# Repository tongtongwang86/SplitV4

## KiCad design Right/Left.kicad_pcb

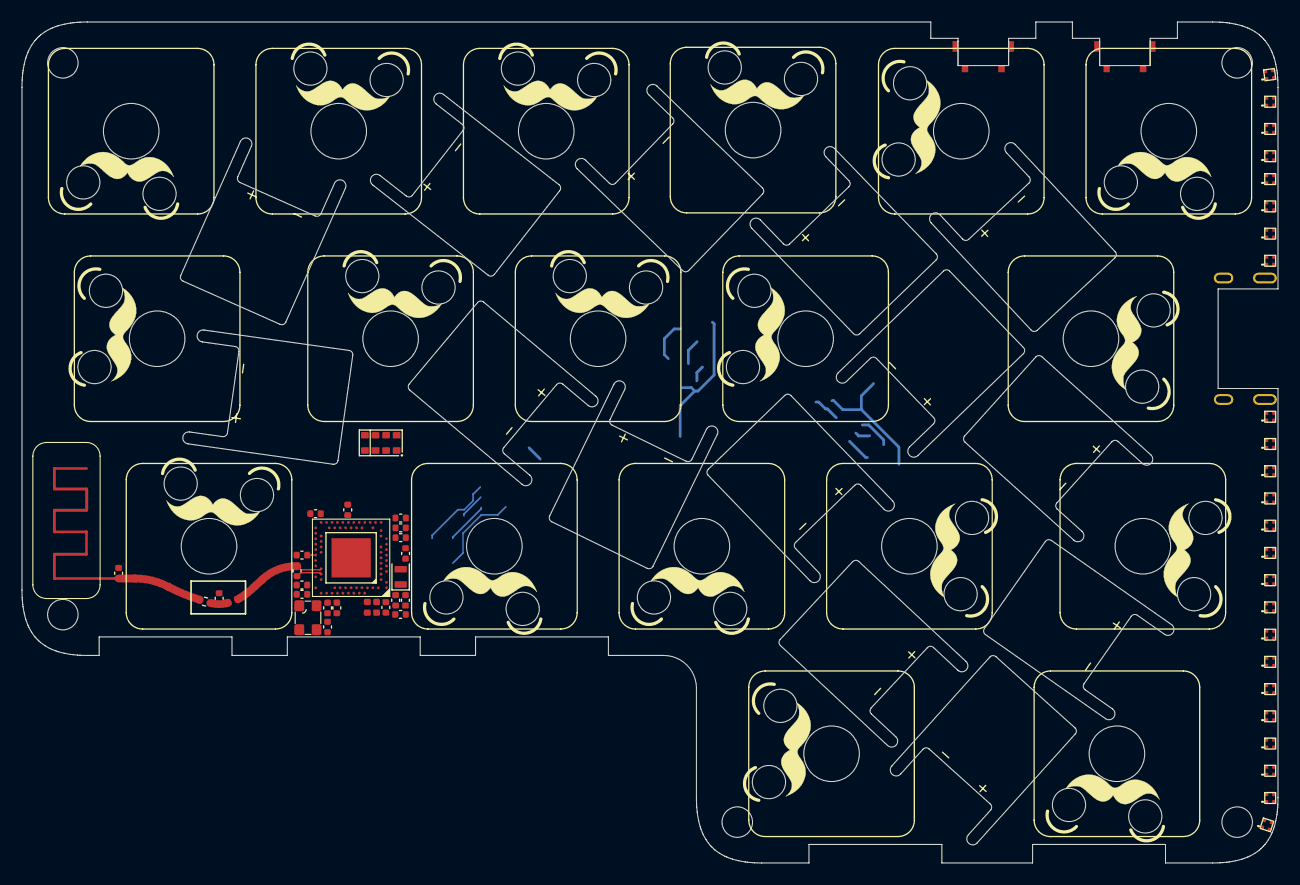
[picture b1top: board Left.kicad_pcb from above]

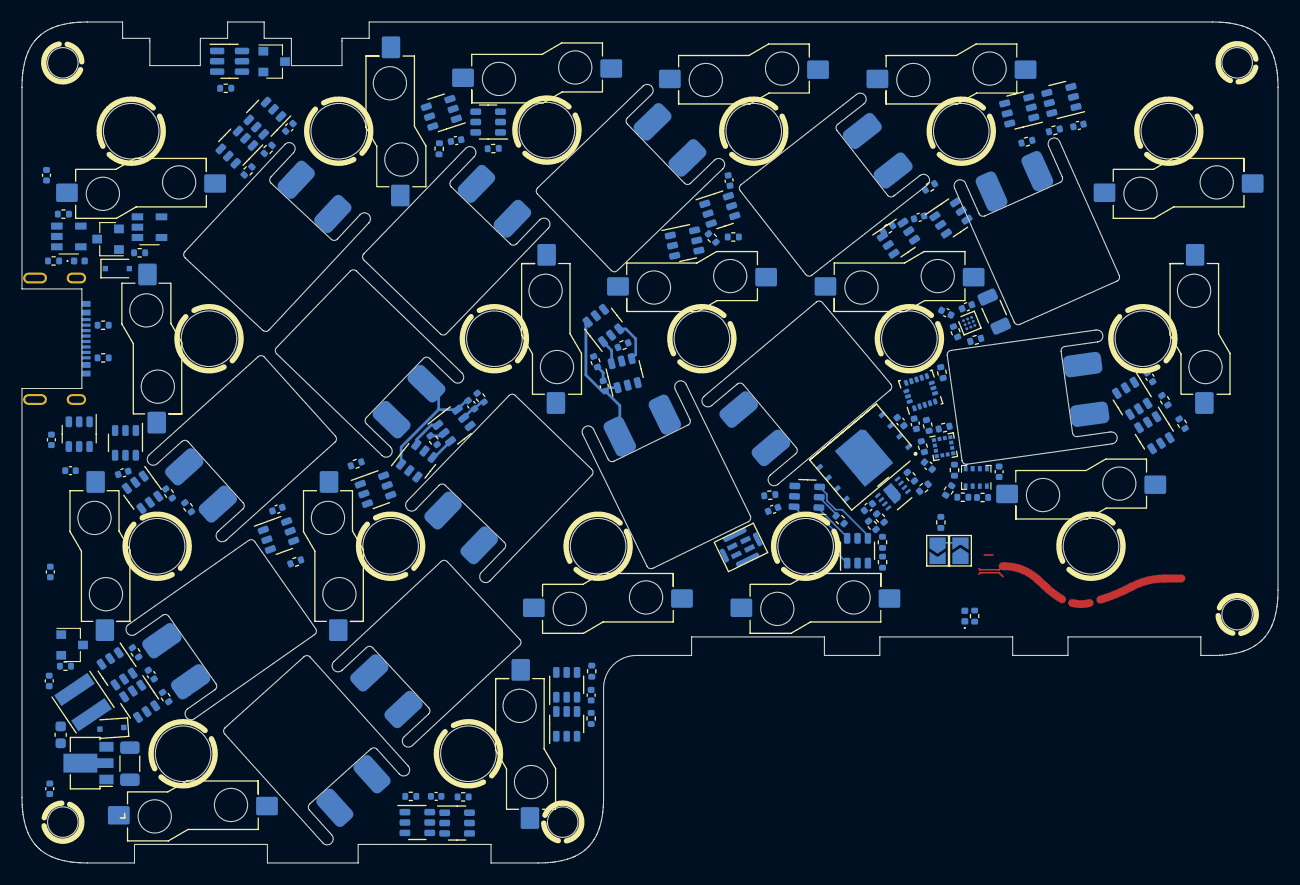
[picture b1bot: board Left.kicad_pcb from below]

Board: 4 copper layers, 115.3 x 77.2 mm, 202 parts (134 on the bottom side), 156 nets.

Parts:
AE1: Antenna; 2.4GHz-meander-antenna-v2
B1, B2, B3, B4, B5, B6, B7, B8, B9, B10, B11, B12, B13, B14: Battery; BatteryV2
C1, C2, C3, C4, C5, C6, C7, C8, C9, C10, C11, C12, C13, C14, C16, C17, C18, C19, C20, C21, C26, C31, C32, C33, C45, C46: 100nF; C_0402_1005Metric
C22, C23, C36, C37: 12pF; C_0402_1005Metric
C24, C25, C27: 4.7uF; C_0402_1005Metric
C28, C29, C47: 1uF; C_0402_1005Metric
C30: 47nF; C_0402_1005Metric
C34: 820pF; C_0402_1005Metric
C35, C39: 1pF; C_0402_1005Metric
C38: 100pF; C_0402_1005Metric
C40: 1.5pF; C_0402_1005Metric
C41: 0.47uF; C_0402_1005Metric
C42, C48, C49: 0.1uF; C_0402_1005Metric
C43: 47uF; C_0603_1608Metric
C44: 100uF; C_1206_3216Metric
D1, D3: 1N5819; D_SOD-323F
D2: BLUE; LED_0402_1005Metric
D4: RED; LED_0402_1005Metric
J1: USB-C USB 2.0 MC-372; USB-C_C168688
JP1, JP2: SolderJumper_2_Open; SolderJumper-2_P1.3mm_Open_TrianglePad1.0x1.5mm
L1: 15nH; L_0402_1005Metric
L2: 10uH; L_0402_1005Metric
L3: 3.9nH; L_0402_1005Metric
L4: 22uH; L_Taiyo-Yuden_NR-40xx
Q1, Q2: AO3407; SOT-23
Q3, Q4, Q5, Q6, Q7, Q8, Q9, Q10, Q19, Q20, Q21, Q22, Q27, Q28: 8205A; SOT-23-6-Small
Q11, Q12, Q13, Q14, Q15, Q16, Q17, Q18, Q23, Q24, Q25, Q26, Q30, Q31: DW01; SOT-23-6-Small
Q33: AO3400A; SOT-23
R1: 100K; R_0402_1005Metric
R2, R33, R34, R35: 5.1K; R_0402_1005Metric
R3, R4, R5, R6, R7, R8, R9, R10, R19, R20, R21, R22, R27, R28, R38, R44: 1K; R_0402_1005Metric
R11, R12, R13, R14, R15, R16, R17, R18, R23, R24, R25, R26, R30, R31: 100; R_0402_1005Metric
R36, R37, R47: 4.7K; R_0402_1005Metric
R39: 0R; R_0402_1005Metric
R40: 820K; R_0402_1005Metric
R41, R46: 2M; R_0402_1005Metric
R42: 0.010; R_1206_3216Metric
R43: 10k; R_0402_1005Metric
R45: 12K; R_0402_1005Metric
R48, R49, R50, R51, R52, R53, R54, R55, R56: 10K; R_0402_1005Metric
TH1: Thermistor_NTC; R_0402_1005Metric
U1: AP2112K-3.3; SOT-23-5
U2, U29: Button
U3: MAX16054; SOT-23-6
U4, U5, U6, U7, U8, U9, U10, U11, U12, U13, U14, U15, U16, U17, U18, U19, U20, U21, U22, U23, U24, U25, U26, U27: WS2812B_-_1010; Led-ARGB
U28: USBLC6-2SC6; SOT-23-6-Small
U30: nRF52840_aQFN73; AQFN-73-1EP_7x7mm_P0.5mm_NRF52840-custom
U31: MAX17055; WLP-9_1.448x1.468mm_Layout3x3_P0.4mm_Ball0.27mm_Pad0.25mm
U32: BL8530_501SM; SOT-89-3
U33: TP4054; SOT-23-5
U34: LSM6DS33; LGA-16_3x3mm_P0.5mm_LayoutBorder3x5y
U35: BMP280; Bosch_LGA-8_2x2.5mm_P0.65mm_ClockwisePinNumbering
U36: SHT30-DIS; Sensirion_DFN-8-1EP_2.5x2.5mm_P0.5mm_EP1.1x1.7mm
U37: APDS-9960
U38: PDM_Mic; SPK0415HM4H
U39: GD25Q; WSON8
U40: LIS3MDL; LGA-12_2x2mm_P0.5mm
X1: 32.768 kHz; Crystal_SMD_2012-2Pin_2.0x1.2mm
X2: 32MHZ; crystal 32mhz

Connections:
/BAROMETRIC/CSB: R48.1, U35.2 (CSB)
/BAROMETRIC/NRF_VDD: C24.2, C25.2, C28.2, C31.2, C32.2, C33.2, C43.1, C45.2, C46.1, C47.2, C48.2, L4.1, R35.2, R36.2, R37.2, R48.2, R49.2, R51.2, R52.2, R53.2, R54.2, R55.2, R56.2, U1.5 (VOUT), U30.A22 (VDD), U30.AD14 (VDD), U30.AD23 (VDD), U30.B1 (VDD), U30.W1 (VDD), U30.Y2 (VDDH), U34.1 (VDDIO), U34.5 (CS), U34.16 (VDD), U35.6 (VDDIO), U35.8 (VDD), U36.5 (VDD), U36.6 (~RESET), U37.5 (LEDA), U37.8 (VDD), U38.1 (VDD), U39.8 (VCC), U40.5 (VDD), U40.6 (VDDIO), U40.10 (CS)
/BAROMETRIC/SDO: R50.2, U35.5 (SDO)
/ExtVcc/GND_EN: Q33.1 (G), R46.1, U30.R1 (TRACEDATA3/P1.09)
/FLASH/QSPI_CS: U30.AD16 (P0.20), U39.1 (SSEL)
/FLASH/QSPI_DATA0: U30.AD12 (P0.17), U39.5 (MOSI)
/FLASH/QSPI_DATA1: U30.AD18 (P0.22), U39.2 (MISO)
/FLASH/QSPI_DATA2: U30.AC19 (P0.23), U39.3 (WP#/IO2)
/FLASH/QSPI_DATA3: U30.AC17 (P0.21), U39.7 (HOLD#/IO3)
/FLASH/QSPI_SCK: U30.AC15 (P0.19), U39.6 (SCK)
/Filter&Reg/VBAT: C42.1, Q1.3 (D), Q2.3 (D), R40.1, U31.B1 (BATT), U33.3 (VBAT)
/FuelGauge/BatteryPin: R40.2, R41.1, U30.J1 (AIN2/P0.04)
/Gyro/Gyro_Interupt: R47.1, U30.B19 (P1.11), U34.7 (INT1)
/LEDLane/DIN: U27.4 (DI), U30.W24 (P1.02)
/LEDLane/Led_Ground: Q33.3 (D), U4.3 (GND), U5.3 (GND), U6.3 (GND), U7.3 (GND), U8.3 (GND), U9.3 (GND), U10.3 (GND), U11.3 (GND), U12.3 (GND), U13.3 (GND), U14.3 (GND), U15.3 (GND), U16.3 (GND), U17.3 (GND), U18.3 (GND), U19.3 (GND), U20.3 (GND), U21.3 (GND), U22.3 (GND), U23.3 (GND), U24.3 (GND), U25.3 (GND), U26.3 (GND), U27.3 (GND)
/LEDLane/Led_Vin: C16.2, C17.2, C18.2, C19.2, C20.2, C44.1, D3.1 (K), U4.2 (VDD), U5.2 (VDD), U6.2 (VDD), U7.2 (VDD), U8.2 (VDD), U9.2 (VDD), U10.2 (VDD), U11.2 (VDD), U12.2 (VDD), U13.2 (VDD), U14.2 (VDD), U15.2 (VDD), U16.2 (VDD), U17.2 (VDD), U18.2 (VDD), U19.2 (VDD), U20.2 (VDD), U21.2 (VDD), U22.2 (VDD), U23.2 (VDD), U24.2 (VDD), U25.2 (VDD), U26.2 (VDD), U27.2 (VDD), U32.2 (OUT)
/LIGHT/APDS_IRQ: R54.1, U30.AD22 (TRACEDATA0/P1.00), U37.2 (INT)
/MCU/BatOffPin: R2.1, U3.3 (CLEAR), U30.Y23 (P1.01)
/MCU/D+: U28.4 (2), U30.AD6 (D+)
/MCU/D-: U28.6 (1), U30.AD4 (D-)
/MCU/PDM_CLK: U30.H2 (P0.27), U38.3 (CLK)
/MCU/PDM_DAT: U30.G1 (P0.26), U38.4 (DATA)
B1-: B1.1 (-), C1.2, Q3.1 (S1), Q11.6 (GND)
B2-: B2.1 (-), C2.2, Q4.1 (S1), Q12.6 (GND)
B3-: B3.1 (-), C3.2, Q5.1 (S1), Q13.6 (GND)
B4-: B4.1 (-), C4.2, Q6.1 (S1), Q14.6 (GND)
B5-: B5.1 (-), C5.2, Q7.1 (S1), Q15.6 (GND)
B6-: B6.1 (-), C6.2, Q8.1 (S1), Q16.6 (GND)
B7-: B7.1 (-), C7.2, Q9.1 (S1), Q17.6 (GND)
B8-: B8.1 (-), C8.2, Q10.1 (S1), Q18.6 (GND)
B9-: B9.1 (-), C9.2, Q19.1 (S1), Q23.6 (GND)
B10-: B10.1 (-), C10.2, Q20.1 (S1), Q24.6 (GND)
B11-: B11.1 (-), C11.2, Q21.1 (S1), Q25.6 (GND)
B12-: B12.1 (-), C12.2, Q22.1 (S1), Q26.6 (GND)
B13-: B13.1 (-), C13.2, Q27.1 (S1), Q30.6 (GND)
B14-: B14.1 (-), C14.2, Q28.1 (S1), Q31.6 (GND)
B+: B1.2 (+), B2.2 (+), B3.2 (+), B4.2 (+), B5.2 (+), B6.2 (+), B7.2 (+), B8.2 (+), B9.2 (+), B10.2 (+), B11.2 (+), B12.2 (+), B13.2 (+), B14.2 (+), Q2.2 (S), R11.1, R12.1, R13.1, R14.1, R15.1, R16.1, R17.1, R18.1, R23.1, R24.1, R25.1, R26.1, R30.1, R31.1, U3.6 (VCC)
CC1: J1.A5 (CC1), R33.1
CC2: J1.B5 (CC2), R34.1
GND: C16.1, C17.1, C18.1, C19.1, C20.1, C21.2, C22.2, C23.2, C24.1, C25.1, C26.1, C27.1, C28.1, C29.2, C30.2, C31.1, C32.1, C33.1, C34.1, C35.1, C36.1, C37.1, C38.2, C39.1, C40.2, C41.1, C42.2, C43.2, C44.2, C45.1, C46.2, C47.1, C48.1, C49.2, J1.A1 (GND), Q33.2 (S), R1.2, R33.2, R34.2, R38.2, R41.2, R42.2, R45.2, R46.2, R47.2, R50.1, U1.2 (GND), U28.2 (G), U29.2, U30.B7 (VSS), U30.EP (VSS), U30.F23 (VSS_PA), U31.A3 (CSN), U32.1 (GND), U33.2 (VSS), U34.4 (SDO), U34.8 (GND), U34.9 (GND), U34.10 (GND), U34.11 (GND), U34.12 (GND), U34.13 (GND), U34.15 (GND), U35.1 (GND), U35.7 (GND), U36.2 (ADDR), U36.7 (R), U36.8 (VSS), U36.9 (VSS), U37.6 (GND), U38.2 (L/R), U38.5 (GND), U38.6 (GND), U38.7 (GND), U38.8 (GND), U39.4 (VSS), U40.2 (GND), U40.3 (GND), U40.9 (SDO), U40.12 (GND), X2.2, X2.4
GND1: Q3.3 (S2), Q4.3 (S2), Q5.3 (S2), Q6.3 (S2), Q7.3 (S2), Q8.3 (S2), Q9.3 (S2), Q10.3 (S2), Q19.3 (S2), Q20.3 (S2), Q21.3 (S2), Q22.3 (S2), Q27.3 (S2), Q28.3 (S2), R2.2, R3.1, R4.1, R5.1, R6.1, R7.1, R8.1, R9.1, R10.1, R19.1, R20.1, R21.1, R22.1, R27.1, R28.1, R42.1, TH1.2, U2.2, U3.2 (GND), U31.C3 (CSP)
unnamed: AE1.1 (A), C40.1, R39.2
unnamed: C1.1, Q11.5 (VCC), R11.2
unnamed: C2.1, Q12.5 (VCC), R12.2
unnamed: C3.1, Q13.5 (VCC), R13.2
unnamed: C4.1, Q14.5 (VCC), R14.2
unnamed: C5.1, Q15.5 (VCC), R15.2
unnamed: C6.1, Q16.5 (VCC), R16.2
unnamed: C7.1, Q17.5 (VCC), R17.2
unnamed: C8.1, Q18.5 (VCC), R18.2
unnamed: C9.1, Q23.5 (VCC), R23.2
unnamed: C10.1, Q24.5 (VCC), R24.2
unnamed: C11.1, Q25.5 (VCC), R25.2
unnamed: C12.1, Q26.5 (VCC), R26.2
unnamed: C13.1, Q30.5 (VCC), R30.2
unnamed: C14.1, Q31.5 (VCC), R31.2
unnamed: C22.1, U30.D2 (XL1/P0.00), X1.1
unnamed: C23.1, U30.F2 (XL2/P0.01), X1.2
unnamed: C26.2, U30.C1 (DEC1)
unnamed: C27.2, U30.AC5 (DECUSB)
unnamed: C29.1, C30.1, L1.1, U30.B5 (DEC4), U30.E24 (DEC6)
unnamed: C34.2, U30.N24 (DEC5)
unnamed: C35.2, L3.1, U30.H23 (ANT)
unnamed: C36.2, U30.A23 (XC2), X2.3
unnamed: C37.2, U30.B24 (XC1), X2.1
unnamed: C38.1, U30.D23 (DEC3)
unnamed: C39.2, L3.2, R39.1
unnamed: C41.2, U31.B3 (REG)
unnamed: C49.1, U40.4 (C1)
unnamed: D1.1 (K), Q1.2 (S), U1.1 (VIN), U1.3 (EN)
unnamed: D2.1 (K), R38.1
unnamed: D2.2 (A), U30.A20 (P1.10)
unnamed: D3.2 (A), L4.2, U32.3 (LX)
unnamed: D4.1 (K), R44.1
unnamed: J1.A6 (D+), J1.B6 (D+), U28.3 (2)
unnamed: J1.A7 (D-), J1.B7 (D-), U28.1
unnamed: JP1.1 (A), JP2.2 (B), R35.1, U29.3
unnamed: JP1.2 (B), U30.P2 (P1.08)
unnamed: JP2.1 (A), U30.AC13 (P0.18/~RESET)
unnamed: L1.2, L2.1
unnamed: L2.2, U30.B3 (DCC)
unnamed: Q2.1 (G), U3.4 (OUT_)
unnamed: Q10.4 (G2), Q18.3 (OC)
unnamed: Q10.6 (G1), Q18.1 (OD)
unnamed: Q3.6 (G1), Q11.1 (OD)
unnamed: Q11.2 (CS), R3.2
unnamed: Q3.4 (G2), Q11.3 (OC)
unnamed: Q4.6 (G1), Q12.1 (OD)
unnamed: Q12.2 (CS), R4.2
unnamed: Q4.4 (G2), Q12.3 (OC)
unnamed: Q5.6 (G1), Q13.1 (OD)
unnamed: Q13.2 (CS), R5.2
unnamed: Q5.4 (G2), Q13.3 (OC)
unnamed: Q6.6 (G1), Q14.1 (OD)
unnamed: Q14.2 (CS), R6.2
unnamed: Q6.4 (G2), Q14.3 (OC)
unnamed: Q7.6 (G1), Q15.1 (OD)
unnamed: Q15.2 (CS), R7.2
unnamed: Q7.4 (G2), Q15.3 (OC)
unnamed: Q8.6 (G1), Q16.1 (OD)
unnamed: Q16.2 (CS), R8.2
unnamed: Q8.4 (G2), Q16.3 (OC)
unnamed: Q9.6 (G1), Q17.1 (OD)
unnamed: Q17.2 (CS), R9.2
unnamed: Q9.4 (G2), Q17.3 (OC)
unnamed: Q18.2 (CS), R10.2
unnamed: Q19.4 (G2), Q23.3 (OC)
unnamed: Q19.6 (G1), Q23.1 (OD)
unnamed: Q20.4 (G2), Q24.3 (OC)
unnamed: Q20.6 (G1), Q24.1 (OD)
unnamed: Q21.4 (G2), Q25.3 (OC)
unnamed: Q21.6 (G1), Q25.1 (OD)
unnamed: Q22.4 (G2), Q26.3 (OC)
unnamed: Q22.6 (G1), Q26.1 (OD)
unnamed: Q23.2 (CS), R19.2
unnamed: Q24.2 (CS), R20.2
unnamed: Q25.2 (CS), R21.2
unnamed: Q26.2 (CS), R22.2
unnamed: Q27.4 (G2), Q30.3 (OC)
unnamed: Q27.6 (G1), Q30.1 (OD)
unnamed: Q28.4 (G2), Q31.3 (OC)
unnamed: Q28.6 (G1), Q31.1 (OD)
unnamed: Q30.2 (CS), R27.2
unnamed: Q31.2 (CS), R28.2
unnamed: R43.1, TH1.1, U31.A1 (AIN)
unnamed: R43.2, U31.C2 (THRM)
unnamed: R44.2, U33.1 (STAT)
unnamed: R45.1, U33.5 (PROG)
unnamed: U2.3, U3.1 (IN)
unnamed: U4.4 (DI), U5.1 (DO)
unnamed: U5.4 (DI), U6.1 (DO)
unnamed: U6.4 (DI), U7.1 (DO)
unnamed: U7.4 (DI), U8.1 (DO)
unnamed: U8.4 (DI), U9.1 (DO)
unnamed: U9.4 (DI), U10.1 (DO)
unnamed: U10.4 (DI), U11.1 (DO)
unnamed: U11.4 (DI), U12.1 (DO)
unnamed: U12.4 (DI), U13.1 (DO)
unnamed: U13.4 (DI), U14.1 (DO)
unnamed: U14.4 (DI), U15.1 (DO)
unnamed: U15.4 (DI), U16.1 (DO)
unnamed: U16.4 (DI), U17.1 (DO)
unnamed: U17.4 (DI), U18.1 (DO)
unnamed: U18.4 (DI), U19.1 (DO)
unnamed: U19.4 (DI), U20.1 (DO)
unnamed: U20.4 (DI), U21.1 (DO)
unnamed: U21.4 (DI), U22.1 (DO)
unnamed: U22.4 (DI), U23.1 (DO)
unnamed: U23.4 (DI), U24.1 (DO)
unnamed: U24.4 (DI), U25.1 (DO)
unnamed: U25.4 (DI), U26.1 (DO)
unnamed: U26.4 (DI), U27.1 (DO)
unnamed: U37.3 (LDR), U37.4 (LEDK)
SCL: R36.1, R49.1, R53.1, R55.1, U30.T2 (TRACEDATA2/P0.11), U31.A2 (SCL), U34.2 (SCL), U35.4 (SCK), U36.4 (SCL), U37.7 (SCL), U40.1 (SCL)
SDA: R37.1, R51.1, R52.1, R56.1, U30.U1 (TRACEDATA1/P0.12), U31.C1 (SDA), U34.3 (SDA), U35.3 (SDI), U36.1 (SDA), U37.1 (SDA), U40.11 (SDA)
VBUS: C21.1, D1.2 (A), D4.2 (A), J1.A4 (VBUS), Q1.1 (G), R1.1, U28.5 (V), U30.AD2 (VBUS), U33.4 (VDD)

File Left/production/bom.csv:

Designator,Footprint,Quantity,Value,LCSC Part #
"B1, B10, B11, B12, B13, B14, B2, B3, B4, B5, B6, B7, B8, B9",BatteryV2,14,Battery,
C1,0402,1,100nF,
C10,0402,1,100nF,
C11,0402,1,100nF,
C12,0402,1,100nF,
C13,0402,1,100nF,
C14,0402,1,100nF,
C16,0402,1,100nF,
C17,0402,1,100nF,
C18,0402,1,100nF,
C19,0402,1,100nF,
C2,0402,1,100nF,
C20,0402,1,100nF,
C21,0402,1,100nF,
C22,0402,1,12pF,
C23,0402,1,12pF,
C24,0402,1,4.7uF,
C25,0402,1,4.7uF,
C26,0402,1,100nF,
C27,0402,1,4.7uF,
C28,0402,1,1uF,
C29,0402,1,1uF,
C3,0402,1,100nF,
C30,0402,1,47nF,
C31,0402,1,100nF,
C32,0402,1,100nF,
C33,0402,1,100nF,
C34,0402,1,820pF,
C35,0402,1,1pF,
C36,0402,1,12pF,
C37,0402,1,12pF,
C38,0402,1,100pF,
C39,0402,1,1pF,
C4,0402,1,100nF,
C40,0402,1,1.5pF,
C41,0402,1,0.47uF,
C42,0402,1,0.1uF,
C43,0603,1,47uF,
C44,1206,1,100uF,
C45,0402,1,100nF,
C46,0402,1,100nF,
C47,0402,1,1uF,
C48,0402,1,0.1uF,
C49,0402,1,0.1uF,
C5,0402,1,100nF,
C6,0402,1,100nF,
C7,0402,1,100nF,
C8,0402,1,100nF,
C9,0402,1,100nF,
"D1, D3",D_SOD-323F,2,1N5819,
D2,0402,1,BLUE,
D4,0402,1,RED,
J1,USB-C_C168688,1,USB-C USB 2.0 MC-372,
"JP1, JP2",SolderBridge,2,SolderJumper_2_Open,
"K1, K10, K11, K12, K13, K14, K15, K16, K17, K18, K2, K3, K4, K5, K6, K7, K8, K9",GateronHotswap,18,KeyboardSwitch,
L1,0402,1,15nH,
L2,0402,1,10uH,
L3,0402,1,3.9nH,
L4,L_Taiyo-Yuden_NR-40xx,1,22uH,
"Q1, Q2",SOT-23,2,AO3407,
"Q10, Q19, Q20, Q21, Q22, Q27, Q28, Q3, Q4, Q5, Q6, Q7, Q8, Q9",SOT-23-6-Small,14,8205A,
"Q11, Q12, Q13, Q14, Q15, Q16, Q17, Q18, Q23, Q24, Q25, Q26, Q30, Q31",SOT-23-6-Small,14,DW01,
Q33,SOT-23,1,AO3400A,
R1,0402,1,100K,
R10,0402,1,1K,
R11,0402,1,100,
R12,0402,1,100,
R13,0402,1,100,
R14,0402,1,100,
R15,0402,1,100,
R16,0402,1,100,
R17,0402,1,100,
R18,0402,1,100,
R19,0402,1,1K,
R2,0402,1,5.1K,
R20,0402,1,1K,
R21,0402,1,1K,
R22,0402,1,1K,
R23,0402,1,100,
R24,0402,1,100,
R25,0402,1,100,
R26,0402,1,100,
R27,0402,1,1K,
R28,0402,1,1K,
R3,0402,1,1K,
R30,0402,1,100,
R31,0402,1,100,
R33,0402,1,5.1K,
R34,0402,1,5.1K,
R35,0402,1,5.1K,
R36,0402,1,4.7K,
R37,0402,1,4.7K,
R38,0402,1,1K,
R39,0402,1,0R,
R4,0402,1,1K,
R40,0402,1,820K,
R41,0402,1,2M,
R42,1206,1,0.010,
R43,0402,1,10k,
R44,0402,1,1K,
R45,0402,1,12K,
R46,0402,1,2M,
R47,0402,1,4.7K,
R48,0402,1,10K,
R49,0402,1,10K,
R5,0402,1,1K,
R50,0402,1,10K,
R51,0402,1,10K,
R52,0402,1,10K,
R53,0402,1,10K,
R54,0402,1,10K,
R55,0402,1,10K,
R56,0402,1,10K,
R6,0402,1,1K,
R7,0402,1,1K,
R8,0402,1,1K,
R9,0402,1,1K,
TH1,0402,1,Thermistor_NTC,
U1,SOT-23-5,1,AP2112K-3.3,
"U10, U11, U12, U13, U14, U15, U16, U17, U18, U19, U20, U21, U22, U23, U24, U25, U26, U27, U4, U5, U6, U7, U8, U9",Led-ARGB,24,WS2812B_-_1010,
"U2, U29",Button,2,Button,
U28,SOT-23-6-Small,1,USBLC6-2SC6,
U3,SOT-23-6,1,MAX16054,
U30,AQFN-73-1EP_7x7mm_P0.5mm_NRF52840-custom,1,nRF52840_aQFN73,
U31,WLP-9_1.448x1.468mm_Layout3x3_P0.4mm_Ball0.27mm_Pad0.25mm,1,MAX17055,
U32,SOT-89-3,1,BL8530_501SM,
U33,SOT-23-5,1,TP4054,
U34,LGA-16_3x3mm_P0.5mm_LayoutBorder3x5y,1,LSM6DS33,
U35,Bosch_LGA-8_2x2.5mm_P0.65mm_ClockwisePinNumbering,1,BMP280,
U36,Sensirion_DFN-8-1EP_2.5x2.5mm_P0.5mm_EP1.1x1.7mm,1,SHT30-DIS,
U37,APDS-9960,1,APDS-9960,
U38,SPK0415HM4H,1,PDM_Mic,
U39,WSON8,1,GD25Q,
U40,LGA-12_2x2mm_P0.5mm,1,LIS3MDL,
X1,Crystal_SMD_2012-2Pin_2.0x1.2mm,1,32.768 kHz,
X2,crystal 32mhz,1,32MHZ,

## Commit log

2023-01-18 worked on left hand
2023-01-19 Finished left hand
2023-01-19 synced backups
2023-01-22 worked on right hand
2023-01-22 routed right hand
2023-01-23 worked on silk screen
2023-01-25 finalizing both hand
2023-01-27 finalize pcb 2
2023-02-16 rounded the tracks
2023-02-20 finalized the combined board
2023-03-06 upgraded files to kicad7
2023-03-06 added ibom
